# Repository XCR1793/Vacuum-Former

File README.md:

# Vacuum Former
An affordable vacuum former capable of forming medium to large bucks and molds. The system must also be safe for anyone to use in both hardware and electronics (as this requires mains).

## Features
* Hybrid Frame - Rigid aluminium combined with cheap cement fiber boards results in a fireproof frame.
* RCBO - Short, fault and overcurrent protection.
* SSR - PWM based temperature control.

## [Hardware](/Hardware/README.md)
The frame is designed to be collapsible so it is easily stored. The heater box, material frame and base plattern uses the same 440mm x 640mm aluminium 2020 frames which makes it easy to
fabricate and assemble. All components that get close to the heatsource is fireproof and areas that are not subject to heat are 3D printed to both save cost and time to construct.

## [Embedded](/Embedded/README.md)
Although dangerous, many safety features were implemented to reduce the risk of injury. This includes breakers and rcbos to detect shorts, faults and if the user accidentally touches the
live wires. All electronics are rated to and beyond what is required to run the system of 240VAC at 20A, this does mean however, that the user must have a port which can supply 15A and
beyond if you want to run the heater box. The average house hold outlet should provide 10A at 240VAC, however if your in the Americas you'll use 110VAC. This means in both senarios,
you will have to find a high current compatible port or else you will trip a breaker. If you dont have one, then you must remove 2 of the heating elements as each of them uses 1KW. This 
will however reduce the total amount of heat you can provided and may not be able to rais the temperature enough to heat difficult to form materials such as polycarbonate which requires 
around 240C to form properly.

## Roadmap
* Milestones: Hardware Assembly Complete
* Milestones: Electrical Wiring
* Milestones: Electrical Box
* Milestones: Controller Box
* Work In Progress: Datasheet
* Planned: Assembly Instructions

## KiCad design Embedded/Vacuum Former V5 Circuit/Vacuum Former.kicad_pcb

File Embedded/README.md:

# Embedded
Embedded Overview - Lorem ipsum dolor sit amet, consectetur adipiscing elit. Ut viverra interdum nisi. In hac habitasse platea dictumst. Integer tincidunt, felis a pellentesque scelerisque, turpis sapien lacinia lectus, eu ultricies nibh leo mollis metus. Nullam a velit condimentum, tempor felis sit amet, euismod lectus. Phasellus sed orci a lectus placerat lacinia sed ac magna. Pellentesque quis mollis dolor. Suspendisse vel imperdiet mauris, a aliquam urna. Ut mattis risus nec sem tincidunt, ac facilisis sem fringilla. Praesent placerat vehicula euismod. Suspendisse volutpat massa id massa facilisis porta.

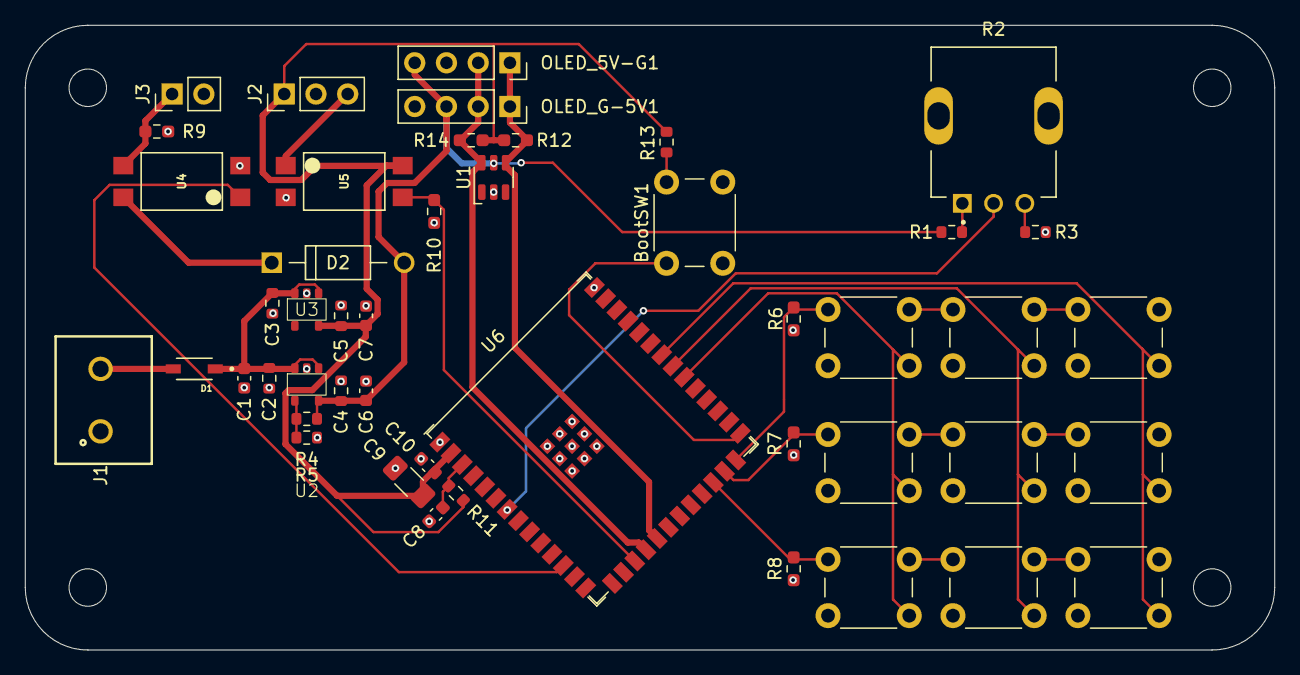
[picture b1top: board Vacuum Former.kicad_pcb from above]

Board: 2 copper layers, 100.0 x 50.0 mm, 47 parts (0 on the bottom side), 24 nets.

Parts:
BootSW1: SW_Push; SW_PUSH_6mm
C1, C6, C7: 10uF; C_0603_1608Metric
C2, C3, C4, C5: 1uF; R_0603_1608Metric
C8: 1uF; C_0603_1608Metric
C9: 22uF; C_1206_3216Metric_Pad1.33x1.80mm_HandSolder
C10: 0.1uF; C_0603_1608Metric
D1: 1N5819HW-7-F; SOD3715X145N
D2: 1N4007; DIOAD1060W80L520D270
J1: 691137710002
J2: Conn_01x03_Pin; PinHeader_1x03_P2.54mm_Vertical
J3: Conn_01x02_Pin; PinHeader_1x02_P2.54mm_Vertical
OLED_5V-G1: Conn_01x04_Socket; PinSocket_1x04_P2.54mm_Vertical
OLED_G-5V1: Conn_01x04_Socket; PinSocket_1x04_P2.54mm_Vertical
R1: 11K; R_0603_1608Metric
R2: PT01-D115D-B103; TRIM_PT01-D115D-B103
R3: 640; R_0603_1608Metric
R4: 63K; R_0603_1608Metric
R5: 12K; R_0603_1608Metric
R6, R7, R8, R12, R14: 10K; R_0603_1608Metric_Pad0.98x0.95mm_HandSolder
R9, R10: 1K; R_0603_1608Metric_Pad0.98x0.95mm_HandSolder
R11, R13: 10K; R_0603_1608Metric
SW1, SW2, SW3, SW4, SW5, SW6, SW7, SW8, SW9: SW_Push; SW_PUSH_6mm
U1: SRV05-4; SOT-23-6-routable
U2: AP7366-W5-7; AP7366
U3: AP7366-33W5-7; AP7366
U4, U5: SMD-PHOTOCOUPLER-5KV-LTV-816S_4P-4.6X6.5MM_; SMD4-2.54-4.6X6.5MM
U6: ESP32-S3-WROOM-1; ESP32-S3-WROOM-1U

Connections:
+3V3: C5.1, C7.1, C9.1, C10.1, J2.1, R11.1, R12.1, R13.1, R14.1, U3.5 (Vout), U5.4, U6.2 (3V3)
+5V: C4.1, C6.1, D2.A, OLED_5V-G1.4, OLED_G-5V1.3, R1.1, R4.1, U1.5 (VP), U2.5 (Vout)
Col1: SW1.2, SW2.2, SW3.2, U6.32 (MTCK/GPIO39/CLK_OUT3/SUBSPICS1)
Col2: SW4.2, SW5.2, SW6.2, U6.33 (MTDO/GPIO40/CLK_OUT2)
Col3: SW7.2, SW8.2, SW9.2, U6.34 (MTDI/GPIO41/CLK_OUT1)
Endstop: R10.1, U5.3, U6.17 (GPIO9/TOUCH9/ADC1_CH8/FSPIHD/SUBSPIHD)
Endstop_Unisolated: J2.3, U5.1
GND: BootSW1.2, C1.2, C2.2, C3.2, C4.2, C5.2, C6.2, C7.2, C8.2, C9.2, C10.2, J1.1, J2.2, J3.2, OLED_5V-G1.3, OLED_G-5V1.4, R3.2, R5.2, R6.1, R7.2, R8.2, R9.2, R10.2, U1.2 (VN), U2.2 (GND), U3.2 (GND), U4.2, U5.2, U6.1 (GND), U6.40 (GND), U6.41 (GND)
Knob: R2.2, U6.7 (GPIO7/TOUCH7/ADC1_CH6)
unnamed: D1.A, J1.2
unnamed: D2.C, U4.4
unnamed: R1.2, R2.1
unnamed: R2.3, R3.1
unnamed: R4.2, R5.1, U2.4 (ADJ)
unnamed: C1.1, C2.1, C3.1, D1.C, U2.1 (VCC), U2.3 (EN), U3.1 (VCC), U3.3 (EN)
unnamed: C8.1, R11.2, U6.3 (EN)
unnamed: BootSW1.1, R13.2, U6.27 (GPIO0/BOOT)
Row1: R6.2, SW1.1, SW4.1, SW7.1, U6.26 (GPIO45)
Row2: R7.1, SW2.1, SW5.1, SW8.1, U6.25 (GPIO48/SPICLK_N/SUBSPICLK_N_DIFF)
Row3: R8.1, SW3.1, SW6.1, SW9.1, U6.24 (GPIO47/SPICLK_P/SUBSPICLK_P_DIFF)
SCL: OLED_5V-G1.2, OLED_G-5V1.2, R14.2, U1.6 (IO4), U6.18 (GPIO10/TOUCH10/ADC1_CH9/FSPICS0/FSPIIO4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)
SDA: OLED_5V-G1.1, OLED_G-5V1.1, R12.2, U1.4 (IO3), U6.19 (GPIO11/TOUCH11/ADC2_CH0/FSPID/FSPIIO5/S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)
SSR_Out: U4.1, U6.12 (GPIO8/TOUCH8/ADC1_CH7/SUBSPICS1)
SSR_Unisolated: J3.1, R9.1, U4.3

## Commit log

2025-01-05 Migrated personal project files into public domain
2025-01-05 Added Vertical Slider & Heater Box Ideation
2025-01-06 Added Base Ideation
2025-01-06 Ideation for Material Clamp
2025-01-07 Worked out material clamping
2025-01-07 Added Electronics High Level Diagram
2025-01-07 Added Overall & Top Down Ideation
2025-01-08 Added Flat T Brackets for Added Rigidity
2025-01-09 Added Material Frame CAD
2025-01-10 More CAD Progress (Completed Heater Box)
2025-01-11 Added More CAD
2025-01-18 Modified Electrical Circuit
2025-01-22 Added Heater Box CAD
2025-01-22 Added Plattern CAD
2025-01-22 Added Main Assembly CAD
2025-01-23 Added Electrical Layout Map
2025-01-23 Updated Readme and Removed Software
2025-01-24 Added labels for design decisions
2025-01-24 Purged Old Diagram Sections
2025-01-25 Added Vacuum Former Handles
2025-01-25 Added Vacuum Former Retainer Pin
2025-01-26 Added BOM & Updated CAD
2025-01-26 Added Total Lengths
2025-01-26 Added Extrusion & Right Angle
2025-01-26 Added Frame Bill of Materials
2025-01-26 Completed BOM (Verification Required before Order)
2025-01-27 Updated BOM before Ordering
2025-02-08 Updated Pricing
2025-02-12 Modified Spreadsheet to reflect IRL Build
2025-02-13 Optimised Heater Box for Ease of Assembly
2025-02-13 Added Tolerances to Vertical Beam Mounts
2025-02-14 Added Tolerances to Platern Supports
2025-02-17 Added Proper Text to README
2025-02-17 Removed Placeholder Electronics Box
2025-02-17 Added Electrical Box
2025-02-18 Added Correct Port Holes
2025-02-18 Added Controller Cable Hole
2025-02-19 Added Control Box & Modified Port Dimensions & Added Mounting Holes
2025-02-20 Modified Box Dimensions to Fit PCB Better
2025-02-21 Added Website Auto Linking test
2025-02-22 Modified Electrical Box Dimensions
2025-02-22 Added Control Box Mount
2025-02-22 Modified model to display accidentally left hidden components
2025-02-23 Modified electrical diagram to match real assembly
2025-02-26 Added Bolt Tolerances
2025-02-27 Added Vacuum Platen Adapter
2025-02-28 Modified Platen for IRL Wood Thickness
2025-02-28 Added Legs
2025-03-02 Added IRL Image to Read Me
2025-03-07 Added Cern OHL V2 License
2025-03-08 Modified Electrical Box to Build Accurate Models
2025-06-14 Modified README (Updated Roadmap)
2025-09-02 Modified File to BOM & Modified links (shortened)
2025-09-04 Added Current vacuum former design
2025-10-31 Modified 3D Printed guide rail mounts
2025-11-02 Modified Platen supports to have easy mounting holes
2025-11-03 Modified File structure to have V5 in V5 folder in preparation for V5.1
2025-11-03 Added To Do List & Migrated Obsolete README.md
